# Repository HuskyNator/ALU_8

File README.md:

# ALU_8
_A tiny 8-bit ALU PCB project._

This project is limited to the use of very simple components, including the use of 7400 IC's with only rudementary behaviour. (This also excludes a clock, though I might add one in the future.)

Note this is a first-time learning project, both with respect to [KiCad](https://www.kicad.org/) and PCB design as a whole. Feel free to give tips or insights!

## Design
>_TODO_

---
### Issues
#### Input Switching:
In an attempt to emulate T-flip-flop-like switching behaviour on the input I've opted to use a leader-follower approach. This is quite bulky & resource intensive. Alternative solutions may include:
- Changing the fysical input mechanic; although I'm unaware of a suitable solution
- Adding a clock & using actual T-flip-flops
- Using an analogue solution; of which there seem multiple, though I'm unsure about the design intricacies involved (especially since this seems unorthodox & design-flaw-sensitive).

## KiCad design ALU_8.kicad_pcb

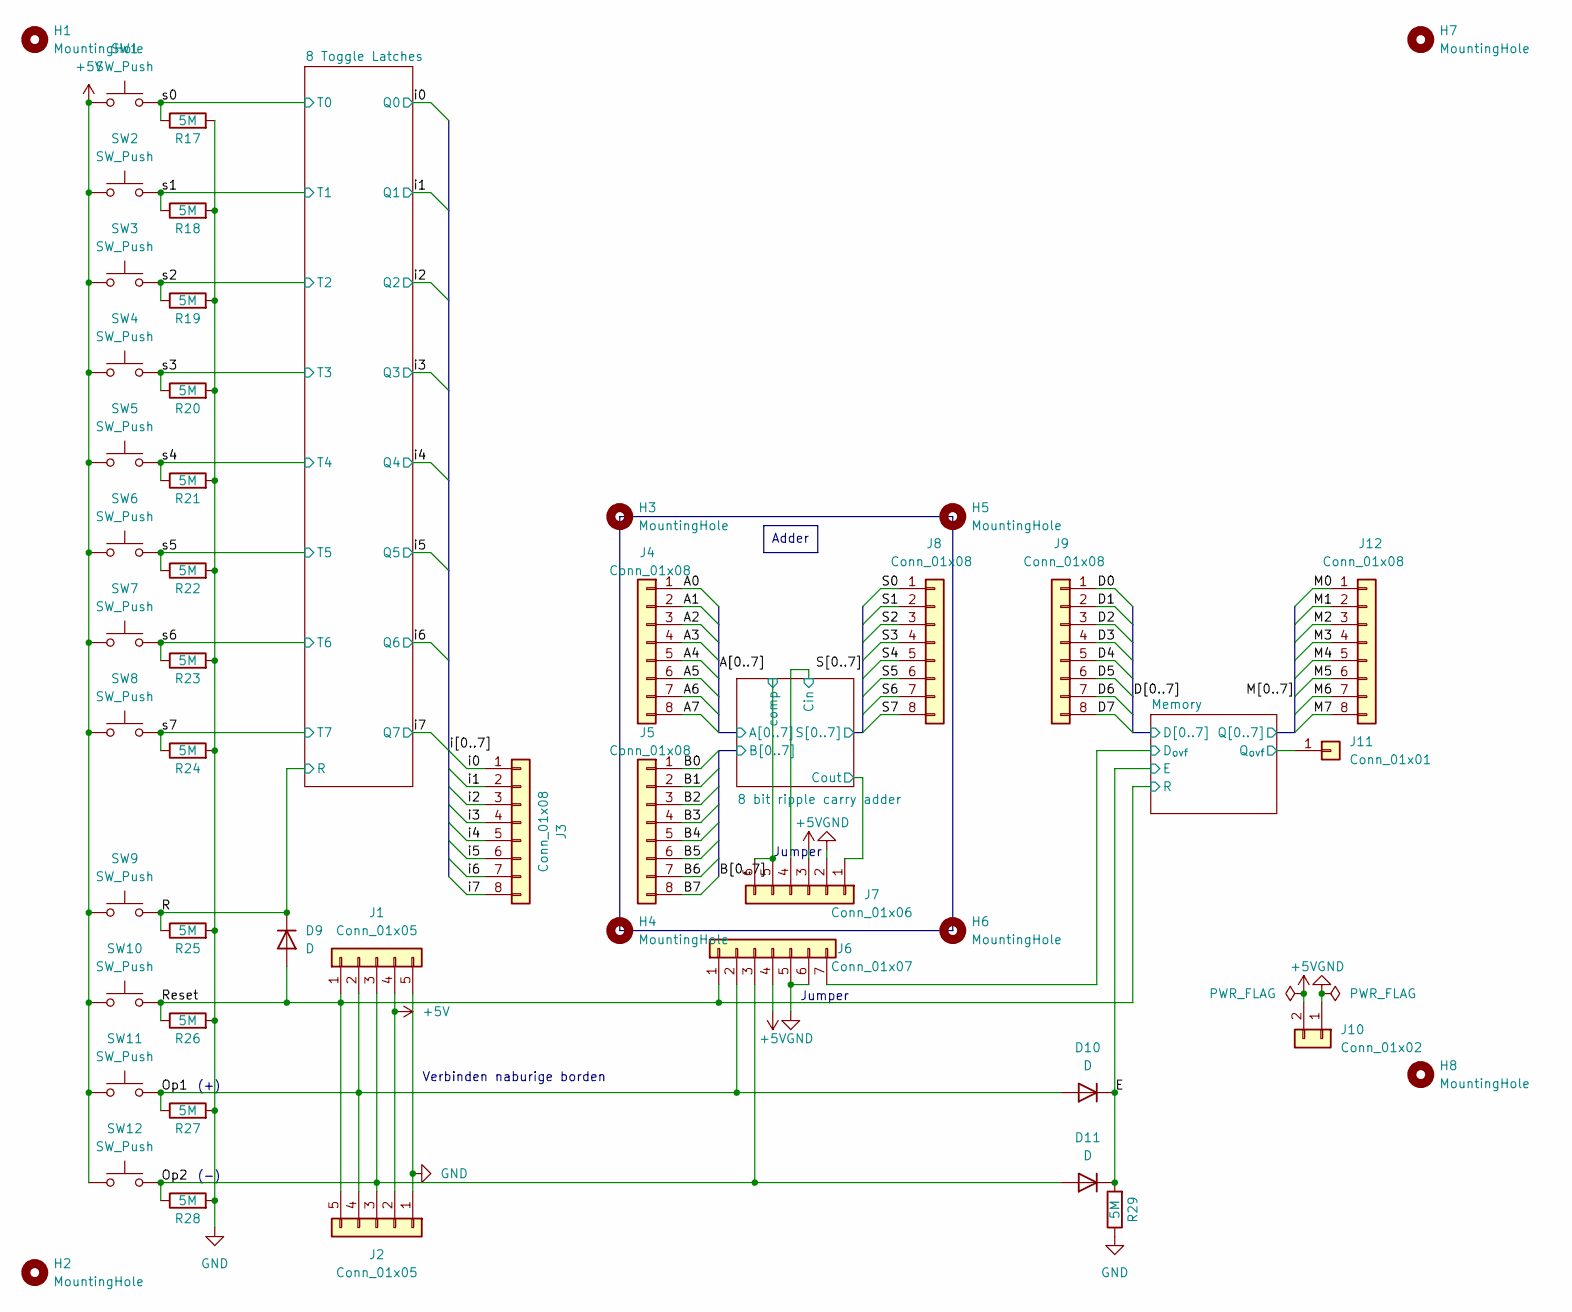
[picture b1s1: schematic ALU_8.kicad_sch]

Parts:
D9, D10, D11: D; D_DO-15_P15.24mm_Horizontal
H1, H2, H3, H4, H5, H6, H7, H8: MountingHole; MountingHole_5mm
J1, J2: Conn_01x05; PinHeader_1x05_P2.54mm_Horizontal
J3, J4, J5, J8, J9, J12: Conn_01x08; PinHeader_1x08_P2.54mm_Vertical
J6: Conn_01x07; PinHeader_1x07_P2.54mm_Vertical
J7: Conn_01x06; PinHeader_1x06_P2.54mm_Vertical
J10: Conn_01x02; PinHeader_1x02_P2.54mm_Vertical
J11: Conn_01x01; PinHeader_1x01_P2.54mm_Vertical
R17, R18, R19, R20, R21, R22, R23, R24, R25, R26, R27, R28, R29: 5M; R_Axial_DIN0207_L6.3mm_D2.5mm_P7.62mm_Horizontal
SW1, SW2, SW3, SW4, SW5, SW6, SW7, SW8, SW9, SW10, SW11, SW12: SW_Push; SW_PUSH_6mm_H13mm

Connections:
+5V: J1.4, J2.2, J6.4, J7.3, J10.2, SW1.1, SW2.1, SW3.1, SW4.1, SW5.1, SW6.1, SW7.1, SW8.1, SW9.1, SW10.1, SW11.1, SW12.1; also elsewhere on the board
/8 bit ripple carry adder/Cin: J7.4; also elsewhere on the board
/8 bit ripple carry adder/Cout: J7.1; also elsewhere on the board
/8 bit ripple carry adder/comp: J7.5, J7.6; also elsewhere on the board
/A0: J4.1; also elsewhere on the board
/A1: J4.2; also elsewhere on the board
/A2: J4.3; also elsewhere on the board
/A3: J4.4; also elsewhere on the board
/A4: J4.5; also elsewhere on the board
/A5: J4.6; also elsewhere on the board
/A6: J4.7; also elsewhere on the board
/A7: J4.8; also elsewhere on the board
/B0: J5.1; also elsewhere on the board
/B1: J5.2; also elsewhere on the board
/B2: J5.3; also elsewhere on the board
/B3: J5.4; also elsewhere on the board
/B4: J5.5; also elsewhere on the board
/B5: J5.6; also elsewhere on the board
/B6: J5.7; also elsewhere on the board
/B7: J5.8; also elsewhere on the board
/D0: J9.1; also elsewhere on the board
/D1: J9.2; also elsewhere on the board
/D2: J9.3; also elsewhere on the board
/D3: J9.4; also elsewhere on the board
/D4: J9.5; also elsewhere on the board
/D5: J9.6; also elsewhere on the board
/D6: J9.7; also elsewhere on the board
/D7: J9.8; also elsewhere on the board
/E: D10.1 (K), D11.1 (K), R29.2; also elsewhere on the board
/M0: J12.1; also elsewhere on the board
/M1: J12.2; also elsewhere on the board
/M2: J12.3; also elsewhere on the board
/M3: J12.4; also elsewhere on the board
/M4: J12.5; also elsewhere on the board
/M5: J12.6; also elsewhere on the board
/M6: J12.7; also elsewhere on the board
/M7: J12.8; also elsewhere on the board
/Memory/D_{ovf}: J6.7; also elsewhere on the board
/Memory/Q_{ovf}: J11.1; also elsewhere on the board
/Op1: D10.2 (A), J1.2, J2.4, J6.2, R27.1, SW11.2
/Op2: D11.2 (A), J1.3, J2.3, J6.3, R28.1, SW12.2
/R: D9.1 (K), R25.1, SW9.2; also elsewhere on the board
/Reset: D9.2 (A), J1.1, J2.5, J6.1, R26.1, SW10.2; also elsewhere on the board
/S0: J8.1; also elsewhere on the board
/S1: J8.2; also elsewhere on the board
/S2: J8.3; also elsewhere on the board
/S3: J8.4; also elsewhere on the board
/S4: J8.5; also elsewhere on the board
/S5: J8.6; also elsewhere on the board
/S6: J8.7; also elsewhere on the board
/S7: J8.8; also elsewhere on the board
/i0: J3.1; also elsewhere on the board
/i1: J3.2; also elsewhere on the board
/i2: J3.3; also elsewhere on the board
/i3: J3.4; also elsewhere on the board
/i4: J3.5; also elsewhere on the board
/i5: J3.6; also elsewhere on the board
/i6: J3.7; also elsewhere on the board
/i7: J3.8; also elsewhere on the board
/s0: R17.1, SW1.2; also elsewhere on the board
/s1: R18.1, SW2.2; also elsewhere on the board
/s2: R19.1, SW3.2; also elsewhere on the board
/s3: R20.1, SW4.2; also elsewhere on the board
/s4: R21.1, SW5.2; also elsewhere on the board
/s5: R22.1, SW6.2; also elsewhere on the board
/s6: R23.1, SW7.2; also elsewhere on the board
/s7: R24.1, SW8.2; also elsewhere on the board
GND: J1.5, J2.1, J6.5, J6.6, J7.2, J10.1, R17.2, R18.2, R19.2, R20.2, R21.2, R22.2, R23.2, R24.2, R25.2, R26.2, R27.2, R28.2, R29.1; also elsewhere on the board

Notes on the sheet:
Adder
(-)
Jumper
Verbinden naburige borden
(+)

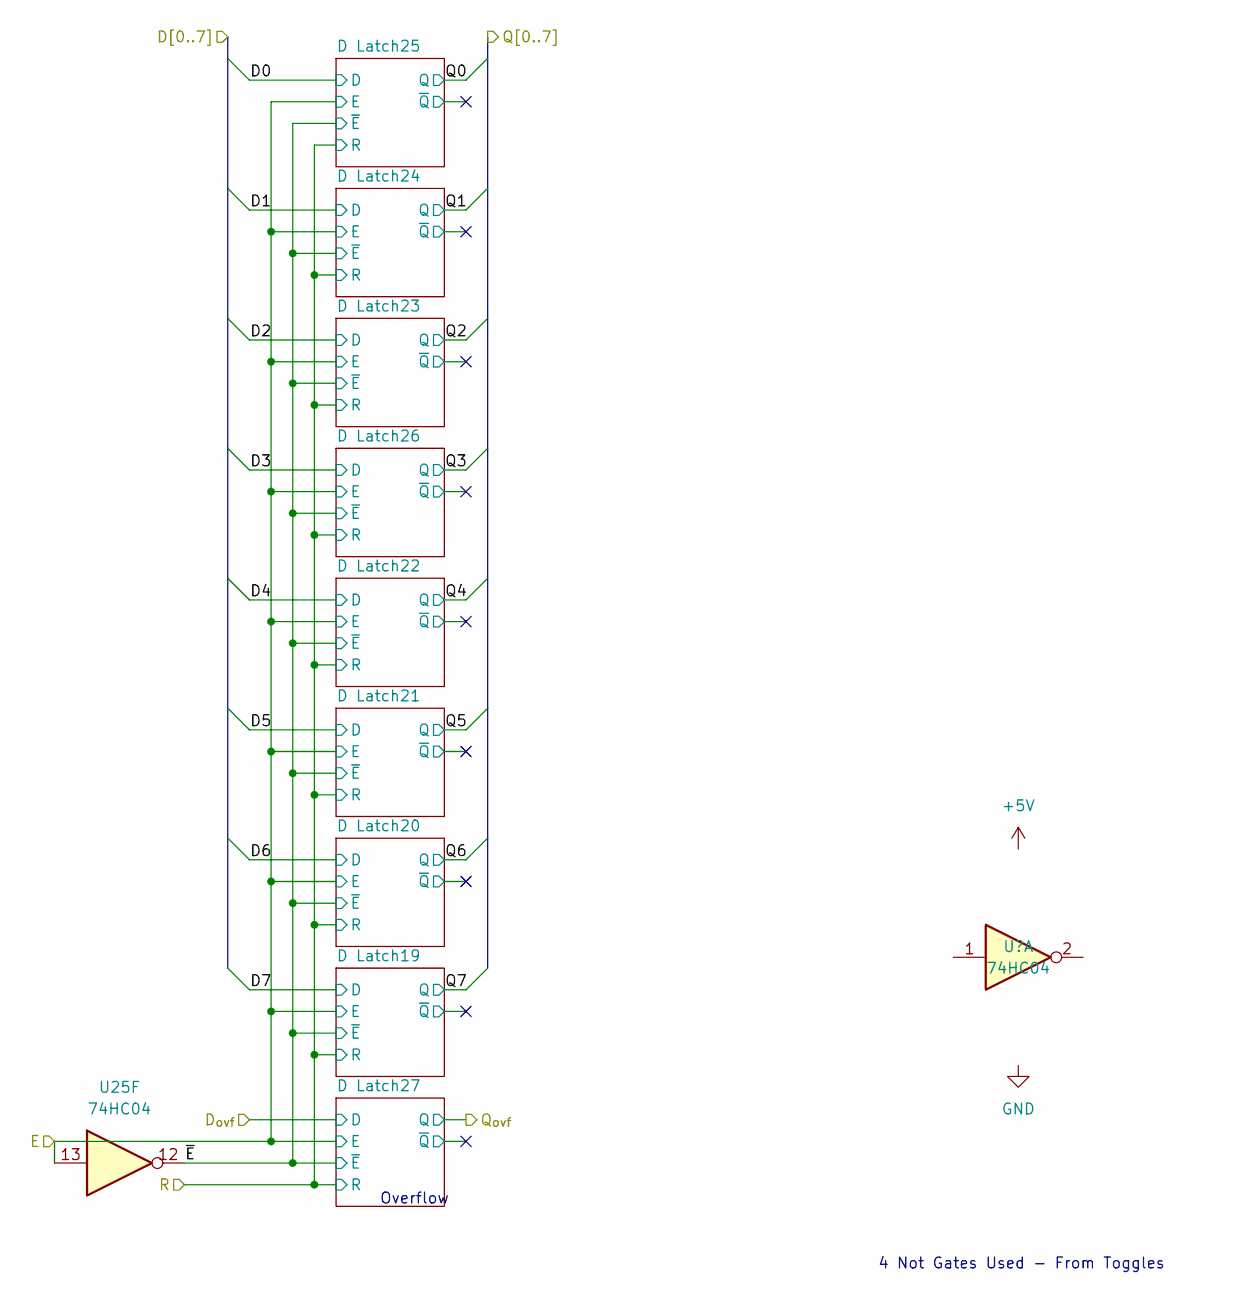
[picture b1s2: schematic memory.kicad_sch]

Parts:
U25: 74HC04; DIP-14_W7.62mm_Socket

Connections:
+5V: U25.14 (VCC); also elsewhere on the board
/D0: U25.1; also elsewhere on the board
/D1: U25.3; also elsewhere on the board
/D2: U25.5; also elsewhere on the board
/D7: U25.9; also elsewhere on the board
/E: U25.13; also elsewhere on the board
/Memory/D_{ovf}: U25.11; also elsewhere on the board
/Memory/~E: U25.12; also elsewhere on the board
GND: U25.7 (GND); also elsewhere on the board
unnamed 248: U25.2; also elsewhere on the board
unnamed 249: U25.4; also elsewhere on the board
unnamed 250: U25.6; also elsewhere on the board
unnamed 251: U25.8; also elsewhere on the board
unnamed 252: U25.10; also elsewhere on the board

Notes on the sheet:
4 Not Gates Used - From Toggles
Overflow

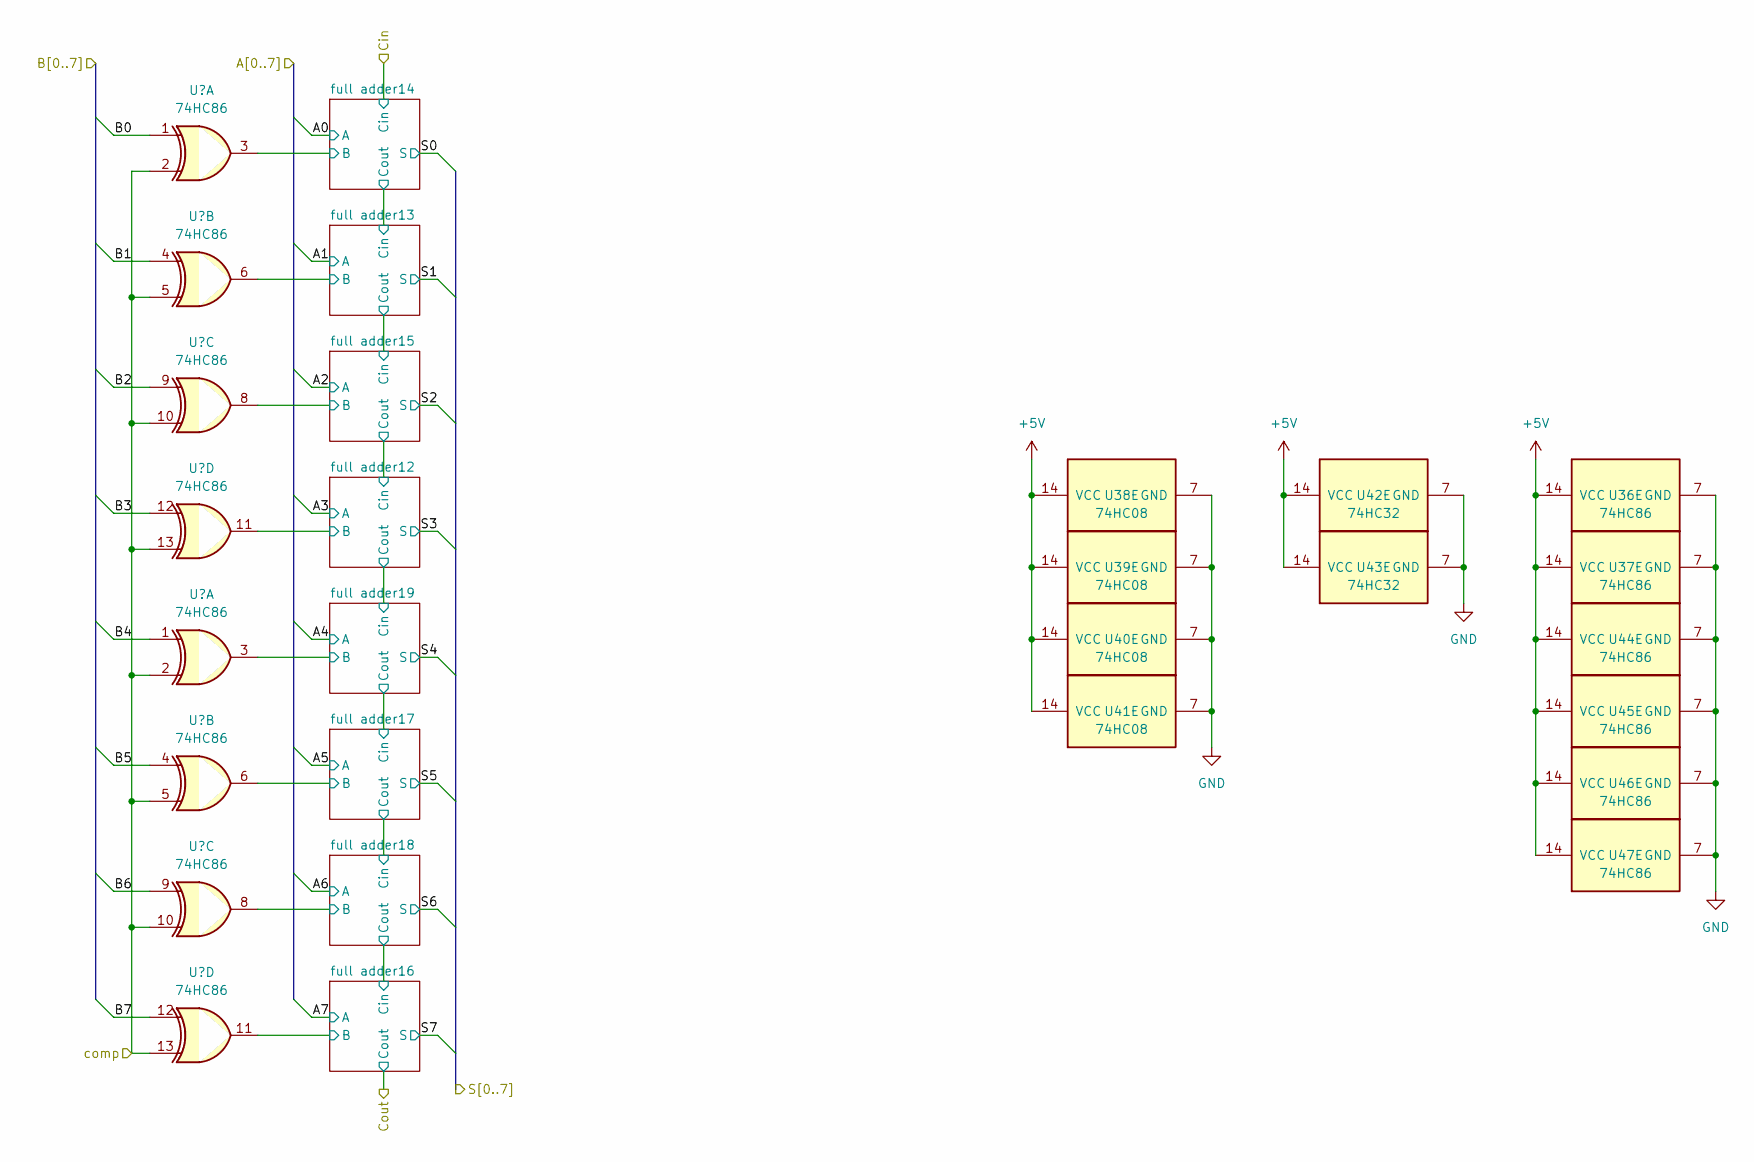
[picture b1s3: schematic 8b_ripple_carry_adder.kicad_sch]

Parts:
U36, U37, U44, U45, U46, U47: 74HC86; DIP-14_W7.62mm_Socket
U38, U39, U40, U41: 74HC08; DIP-14_W7.62mm_Socket
U42, U43: 74HC32; DIP-14_W7.62mm_Socket

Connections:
+5V: U36.14 (VCC), U37.14 (VCC), U38.14 (VCC), U39.14 (VCC), U40.14 (VCC), U41.14 (VCC), U42.14 (VCC), U43.14 (VCC), U44.14 (VCC), U45.14 (VCC), U46.14 (VCC), U47.14 (VCC); also elsewhere on the board
/8 bit ripple carry adder/Cout: U43.11; also elsewhere on the board
/8 bit ripple carry adder/comp: U36.2, U36.5, U36.10, U36.13, U37.2, U37.5, U37.10, U37.13; also elsewhere on the board
/8 bit ripple carry adder/full adder12/B: U36.11, U38.10, U44.12
/8 bit ripple carry adder/full adder12/Cin: U39.10, U42.8, U45.12
/8 bit ripple carry adder/full adder12/Cout: U42.11; also elsewhere on the board
/8 bit ripple carry adder/full adder12/g: U38.8, U42.12
/8 bit ripple carry adder/full adder12/p: U39.9, U44.11, U45.13
/8 bit ripple carry adder/full adder13/B: U36.6, U38.5, U44.4
/8 bit ripple carry adder/full adder13/Cin: U39.5, U45.4; also elsewhere on the board
/8 bit ripple carry adder/full adder13/Cout: U39.13, U42.6, U45.9
/8 bit ripple carry adder/full adder13/g: U38.6, U42.4
/8 bit ripple carry adder/full adder13/p: U39.4, U44.6, U45.5
/8 bit ripple carry adder/full adder14/B: U36.3; also elsewhere on the board
/8 bit ripple carry adder/full adder15/B: U36.8, U38.13, U44.9
/8 bit ripple carry adder/full adder15/g: U38.11, U42.9
/8 bit ripple carry adder/full adder15/p: U39.12, U44.8, U45.10
/8 bit ripple carry adder/full adder16/B: U37.11, U41.10, U46.12
/8 bit ripple carry adder/full adder16/Cin: U43.8, U47.12; also elsewhere on the board
/8 bit ripple carry adder/full adder16/g: U41.8, U43.12
/8 bit ripple carry adder/full adder16/p: U46.11, U47.13; also elsewhere on the board
/8 bit ripple carry adder/full adder17/B: U37.6, U41.5, U46.4
/8 bit ripple carry adder/full adder17/Cin: U47.4; also elsewhere on the board
/8 bit ripple carry adder/full adder17/Cout: U43.6, U47.9; also elsewhere on the board
/8 bit ripple carry adder/full adder17/g: U41.6, U43.4
/8 bit ripple carry adder/full adder17/p: U46.6, U47.5; also elsewhere on the board
/8 bit ripple carry adder/full adder18/B: U37.8, U41.13, U46.9
/8 bit ripple carry adder/full adder18/g: U41.11, U43.9
/8 bit ripple carry adder/full adder18/p: U46.8, U47.10; also elsewhere on the board
/8 bit ripple carry adder/full adder19/B: U37.3; also elsewhere on the board
/A1: U38.4, U44.5; also elsewhere on the board
/A2: U38.12, U44.10; also elsewhere on the board
/A3: U38.9, U44.13; also elsewhere on the board
/A5: U41.4, U46.5; also elsewhere on the board
/A6: U41.12, U46.10; also elsewhere on the board
/A7: U41.9, U46.13; also elsewhere on the board
/B0: U36.1; also elsewhere on the board
/B1: U36.4; also elsewhere on the board
/B2: U36.9; also elsewhere on the board
/B3: U36.12; also elsewhere on the board
/B4: U37.1; also elsewhere on the board
/B5: U37.4; also elsewhere on the board
/B6: U37.9; also elsewhere on the board
/B7: U37.12; also elsewhere on the board
/S1: U45.6; also elsewhere on the board
/S2: U45.8; also elsewhere on the board
/S3: U45.11; also elsewhere on the board
/S5: U47.6; also elsewhere on the board
/S6: U47.8; also elsewhere on the board
/S7: U47.11; also elsewhere on the board
GND: U36.7 (GND), U37.7 (GND), U38.7 (GND), U39.7 (GND), U40.7 (GND), U41.7 (GND), U42.7 (GND), U43.7 (GND), U44.7 (GND), U45.7 (GND), U46.7 (GND), U47.7 (GND); also elsewhere on the board
unnamed: U39.6, U42.5
unnamed: U39.8, U42.13
unnamed: U39.11, U42.10
unnamed 288: U43.5; also elsewhere on the board
unnamed 289: U43.10; also elsewhere on the board
unnamed 290: U43.13; also elsewhere on the board

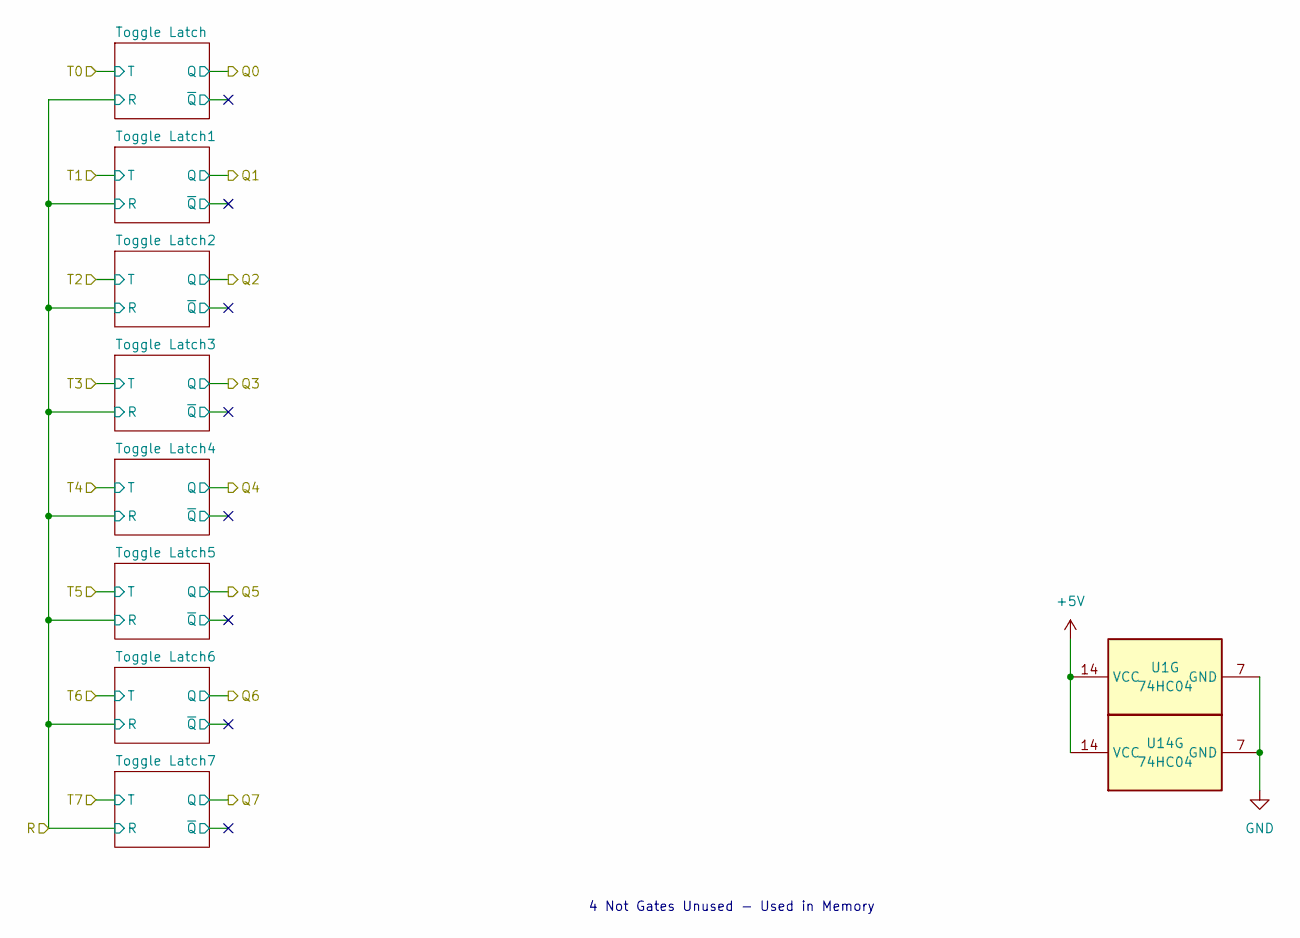
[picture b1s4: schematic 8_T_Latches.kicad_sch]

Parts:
U1, U14: 74HC04; DIP-14_W7.62mm_Socket

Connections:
+5V: U1.14 (VCC), U14.14 (VCC); also elsewhere on the board
/D3: U14.9; also elsewhere on the board
/D4: U14.11; also elsewhere on the board
/D5: U14.13; also elsewhere on the board
/D6: U14.5; also elsewhere on the board
/s1: U1.3; also elsewhere on the board
/s2: U1.5; also elsewhere on the board
/s3: U1.9; also elsewhere on the board
/s4: U1.11; also elsewhere on the board
/s5: U1.13; also elsewhere on the board
/s7: U14.3; also elsewhere on the board
GND: U1.7 (GND), U14.7 (GND); also elsewhere on the board
unnamed 174: U1.4; also elsewhere on the board
unnamed 175: U1.6; also elsewhere on the board
unnamed 176: U1.8; also elsewhere on the board
unnamed 177: U1.10; also elsewhere on the board
unnamed 178: U1.12; also elsewhere on the board
unnamed 216: U14.4; also elsewhere on the board
unnamed 217: U14.6; also elsewhere on the board
unnamed 218: U14.8; also elsewhere on the board
unnamed 219: U14.10; also elsewhere on the board
unnamed 220: U14.12; also elsewhere on the board

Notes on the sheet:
4 Not Gates Unused - Used in Memory

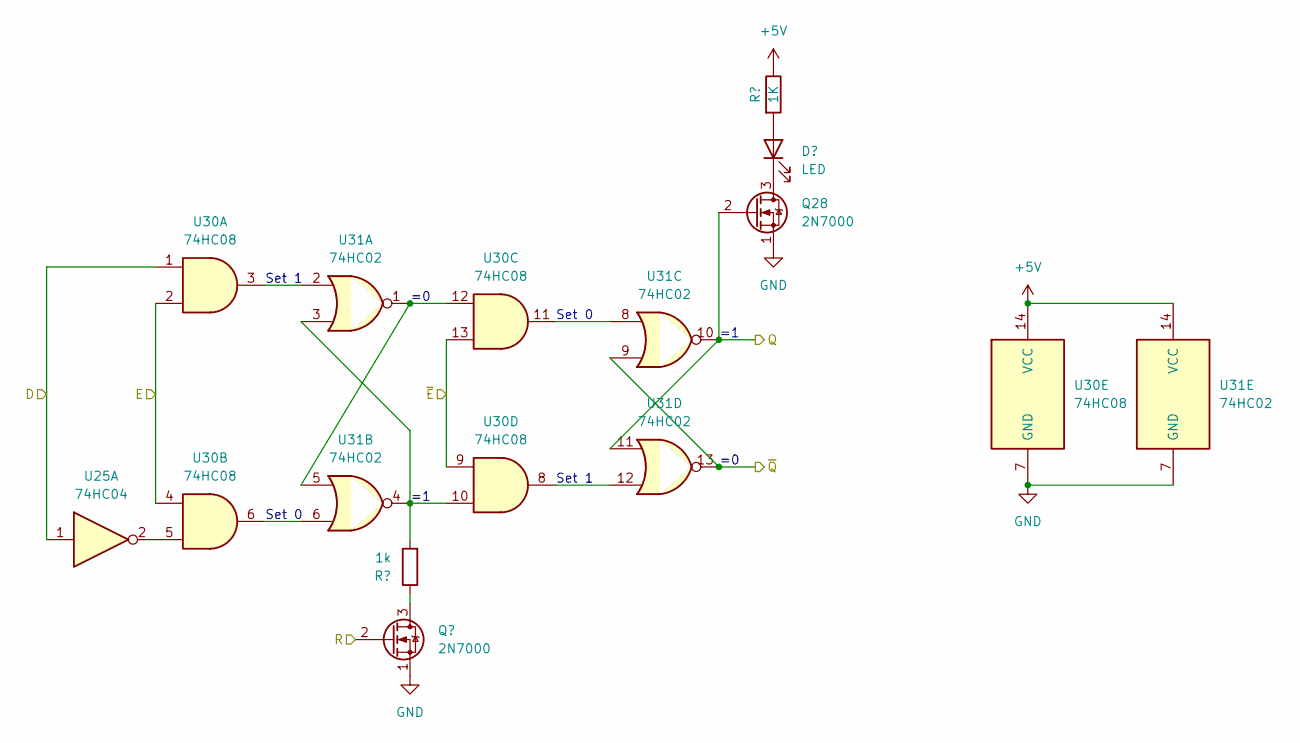
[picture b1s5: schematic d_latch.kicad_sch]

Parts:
D12: LED; D_DO-34_SOD68_P2.54mm_Vertical_KathodeUp
Q17, Q28: 2N7000; TO-92_Inline
R30: 1k; R_Axial_DIN0207_L6.3mm_D2.5mm_P7.62mm_Horizontal
R31: 1K; R_Axial_DIN0207_L6.3mm_D2.5mm_P7.62mm_Horizontal
U25: 74HC04; DIP-14_W7.62mm_Socket
U30: 74HC08; DIP-14_W7.62mm_Socket
U31: 74HC02; DIP-14_W7.62mm_Socket

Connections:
+5V: R31.1, U25.14 (VCC), U30.14 (VCC), U31.14 (VCC); also elsewhere on the board
/D0: U25.1, U30.1; also elsewhere on the board
/D1: U25.3; also elsewhere on the board
/D2: U25.5; also elsewhere on the board
/D7: U25.9; also elsewhere on the board
/E: U30.2, U30.4; also elsewhere on the board
/M0: Q28.2 (G), U31.10, U31.11; also elsewhere on the board
/Memory/D Latch25/~Q: U31.9, U31.13
/Memory/D_{ovf}: U25.11; also elsewhere on the board
/Memory/~E: U30.9, U30.13; also elsewhere on the board
/Reset: Q17.2 (G); also elsewhere on the board
GND: Q17.1 (S), Q28.1 (S), U25.7 (GND), U30.7 (GND), U31.7 (GND); also elsewhere on the board
unnamed: D12.2 (A), R31.2
unnamed: Q17.3 (D), R30.1
unnamed: U25.2, U30.5
unnamed 249: U25.4; also elsewhere on the board
unnamed 250: U25.6; also elsewhere on the board
unnamed 251: U25.8; also elsewhere on the board
unnamed 252: U25.10; also elsewhere on the board
unnamed: U30.3, U31.2
unnamed: U30.6, U31.6
unnamed: U30.8, U31.12
unnamed: U30.11, U31.8
unnamed: U30.12, U31.1, U31.5

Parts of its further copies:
D13, D14, D15, D16, D17, D18, D19, D20: LED; D_DO-34_SOD68_P2.54mm_Vertical_KathodeUp
Q18, Q19, Q20, Q21, Q22, Q23, Q24, Q25, Q26, Q27, Q29, Q30, Q31, Q32, Q33, Q34: 2N7000; TO-92_Inline
R32, R34, R36, R38, R40, R42, R44, R46: 1k; R_Axial_DIN0207_L6.3mm_D2.5mm_P7.62mm_Horizontal
R33, R35, R37, R39, R41, R43, R45, R47: 1K; R_Axial_DIN0207_L6.3mm_D2.5mm_P7.62mm_Horizontal
U19, U21, U23, U26, U28, U32, U34, U49: 74HC08; DIP-14_W7.62mm_Socket
U20, U22, U24, U27, U29, U33, U35, U48: 74HC02; DIP-14_W7.62mm_Socket

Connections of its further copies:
+5V: R33.1, R35.1, R37.1, R39.1, R41.1, R43.1, R45.1, R47.1, U19.14 (VCC), U20.14 (VCC), U21.14 (VCC), U22.14 (VCC), U23.14 (VCC), U24.14 (VCC), U26.14 (VCC), U27.14 (VCC), U28.14 (VCC), U29.14 (VCC), U32.14 (VCC), U33.14 (VCC), U34.14 (VCC), U35.14 (VCC), U48.14 (VCC), U49.14 (VCC); also elsewhere on the board
/8 bit ripple carry adder/full adder12/Cout: U49.2; also elsewhere on the board
/8 bit ripple carry adder/full adder16/Cin: U49.10; also elsewhere on the board
/8 bit ripple carry adder/full adder16/p: U49.9; also elsewhere on the board
/8 bit ripple carry adder/full adder17/Cin: U49.5; also elsewhere on the board
/8 bit ripple carry adder/full adder17/Cout: U49.13; also elsewhere on the board
/8 bit ripple carry adder/full adder17/p: U49.4; also elsewhere on the board
/8 bit ripple carry adder/full adder18/p: U49.12; also elsewhere on the board
/8 bit ripple carry adder/full adder19/p: U49.1; also elsewhere on the board
/D1: U28.1; also elsewhere on the board
/D2: U26.1; also elsewhere on the board
/D3: U32.1; also elsewhere on the board
/D4: U23.1; also elsewhere on the board
/D5: U21.1; also elsewhere on the board
/D6: U19.1; also elsewhere on the board
/E: U19.2, U19.4, U21.2, U21.4, U23.2, U23.4, U26.2, U26.4, U28.2, U28.4, U32.2, U32.4, U34.2, U34.4; also elsewhere on the board
/M1: Q26.2 (G), U29.10, U29.11; also elsewhere on the board
/M2: Q24.2 (G), U27.10, U27.11; also elsewhere on the board
/M3: Q30.2 (G), U33.10, U33.11; also elsewhere on the board
/M4: Q22.2 (G), U24.10, U24.11; also elsewhere on the board
/M5: Q20.2 (G), U22.10, U22.11; also elsewhere on the board
/M6: Q18.2 (G), U20.10, U20.11; also elsewhere on the board
/M7: Q34.2 (G), U48.10, U48.11; also elsewhere on the board
/Memory/D Latch19/~Q: U48.9, U48.13
/Memory/D Latch20/~Q: U20.9, U20.13
/Memory/D Latch21/~Q: U22.9, U22.13
/Memory/D Latch22/~Q: U24.9, U24.13
/Memory/D Latch23/~Q: U27.9, U27.13
/Memory/D Latch24/~Q: U29.9, U29.13
/Memory/D Latch26/~Q: U33.9, U33.13
/Memory/D Latch27/~Q: U35.9, U35.13
/Memory/D_{ovf}: U34.1; also elsewhere on the board
/Memory/Q_{ovf}: Q32.2 (G), U35.10, U35.11; also elsewhere on the board
/Memory/~E: U19.9, U19.13, U21.9, U21.13, U23.9, U23.13, U26.9, U26.13, U28.9, U28.13, U32.9, U32.13, U34.9, U34.13; also elsewhere on the board
/Reset: Q19.2 (G), Q21.2 (G), Q23.2 (G), Q25.2 (G), Q27.2 (G), Q29.2 (G), Q31.2 (G), Q33.2 (G); also elsewhere on the board
GND: Q18.1 (S), Q19.1 (S), Q20.1 (S), Q21.1 (S), Q22.1 (S), Q23.1 (S), Q24.1 (S), Q25.1 (S), Q26.1 (S), Q27.1 (S), Q29.1 (S), Q30.1 (S), Q31.1 (S), Q32.1 (S), Q33.1 (S), Q34.1 (S), U19.7 (GND), U20.7 (GND), U21.7 (GND), U22.7 (GND), U23.7 (GND), U24.7 (GND), U26.7 (GND), U27.7 (GND), U28.7 (GND), U29.7 (GND), U32.7 (GND), U33.7 (GND), U34.7 (GND), U35.7 (GND), U48.7 (GND), U49.7 (GND); also elsewhere on the board
unnamed: D13.2 (A), R33.2
unnamed: D13.1 (K), Q20.3 (D)
unnamed: D14.2 (A), R35.2
unnamed: D14.1 (K), Q22.3 (D)
unnamed: D15.2 (A), R37.2
unnamed: D15.1 (K), Q24.3 (D)
unnamed: D16.2 (A), R39.2
unnamed: D16.1 (K), Q26.3 (D)
unnamed: D17.2 (A), R41.2
unnamed: D18.2 (A), R43.2
unnamed: D18.1 (K), Q30.3 (D)
unnamed: D19.2 (A), R45.2
unnamed: D19.1 (K), Q32.3 (D)
unnamed: D20.2 (A), R47.2
unnamed: D20.1 (K), Q34.3 (D)
unnamed: Q19.3 (D), R32.1
unnamed: Q21.3 (D), R34.1
unnamed: Q23.3 (D), R36.1
unnamed: Q25.3 (D), R38.1
unnamed: Q27.3 (D), R40.1
unnamed: Q29.3 (D), R42.1
unnamed: Q31.3 (D), R44.1
unnamed: Q33.3 (D), R46.1
unnamed: R32.2, U21.10, U22.3, U22.4
unnamed 167: R34.2, U23.10, U24.3, U24.4; also elsewhere on the board
unnamed: R36.2, U26.10, U27.3, U27.4
unnamed: R38.2, U28.10, U29.3, U29.4
unnamed: R42.2, U32.10, U33.3, U33.4
unnamed: R44.2, U34.10, U35.3, U35.4
unnamed 172: R46.2, U48.3, U48.4; also elsewhere on the board
unnamed 217: U19.5; also elsewhere on the board
unnamed 218: U32.5; also elsewhere on the board
unnamed 219: U23.5; also elsewhere on the board
unnamed 220: U21.5; also elsewhere on the board
unnamed: U19.3, U20.2
unnamed: U19.6, U20.6
unnamed: U19.8, U20.12
unnamed: U19.11, U20.8
unnamed: U19.12, U20.1, U20.5
unnamed: U21.3, U22.2
unnamed: U21.6, U22.6
unnamed: U21.8, U22.12
unnamed: U21.11, U22.8
unnamed: U21.12, U22.1, U22.5
unnamed 243: U23.3, U24.2; also elsewhere on the board
unnamed 244: U23.6, U24.6; also elsewhere on the board
unnamed 245: U23.8, U24.12; also elsewhere on the board
unnamed 246: U23.11, U24.8; also elsewhere on the board
unnamed 247: U23.12, U24.1, U24.5; also elsewhere on the board
unnamed 249: U28.5; also elsewhere on the board
unnamed 250: U26.5; also elsewhere on the board
unnamed 252: U34.5; also elsewhere on the board
unnamed: U26.3, U27.2
unnamed: U26.6, U27.6
unnamed: U26.8, U27.12
unnamed: U26.11, U27.8
unnamed: U26.12, U27.1, U27.5
unnamed: U28.3, U29.2
unnamed: U28.6, U29.6
unnamed: U28.8, U29.12
unnamed: U28.11, U29.8
unnamed: U28.12, U29.1, U29.5
unnamed: U32.3, U33.2
unnamed: U32.6, U33.6
unnamed: U32.8, U33.12
unnamed: U32.11, U33.8
unnamed: U32.12, U33.1, U33.5
unnamed: U34.3, U35.2
unnamed: U34.6, U35.6
unnamed: U34.8, U35.12
unnamed: U34.11, U35.8
unnamed: U34.12, U35.1, U35.5
unnamed 282: U48.2; also elsewhere on the board
unnamed 283: U48.6; also elsewhere on the board
unnamed 284: U48.12; also elsewhere on the board
unnamed 285: U48.8; also elsewhere on the board
unnamed 286: U48.1, U48.5; also elsewhere on the board
unnamed 287: U49.3; also elsewhere on the board
unnamed 288: U49.6; also elsewhere on the board
unnamed 289: U49.11; also elsewhere on the board
unnamed 290: U49.8; also elsewhere on the board

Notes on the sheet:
Set 0
Set 1

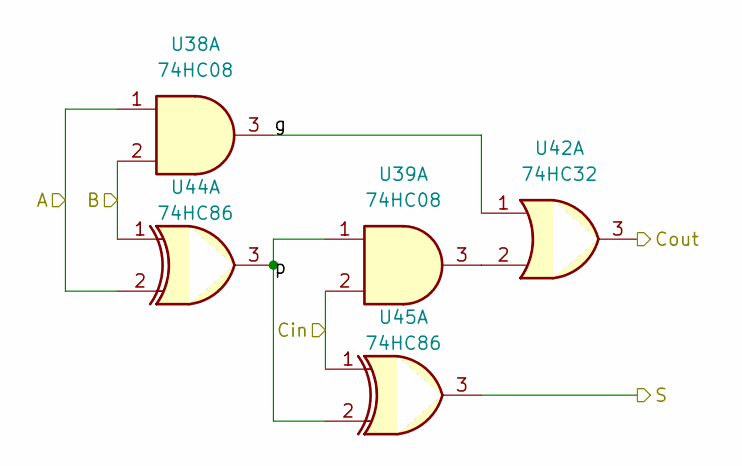
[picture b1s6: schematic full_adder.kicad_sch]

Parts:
U38, U39: 74HC08; DIP-14_W7.62mm_Socket
U42: 74HC32; DIP-14_W7.62mm_Socket
U44, U45: 74HC86; DIP-14_W7.62mm_Socket

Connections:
/8 bit ripple carry adder/Cin: U39.2, U45.1; also elsewhere on the board
/8 bit ripple carry adder/full adder12/B: U38.10, U44.12; also elsewhere on the board
/8 bit ripple carry adder/full adder12/Cin: U39.10, U42.8, U45.12
/8 bit ripple carry adder/full adder12/Cout: U42.11; also elsewhere on the board
/8 bit ripple carry adder/full adder12/g: U38.8, U42.12
/8 bit ripple carry adder/full adder12/p: U39.9, U44.11, U45.13
/8 bit ripple carry adder/full adder13/B: U38.5, U44.4; also elsewhere on the board
/8 bit ripple carry adder/full adder13/Cin: U39.5, U42.3, U45.4
/8 bit ripple carry adder/full adder13/Cout: U39.13, U42.6, U45.9
/8 bit ripple carry adder/full adder13/g: U38.6, U42.4
/8 bit ripple carry adder/full adder13/p: U39.4, U44.6, U45.5
/8 bit ripple carry adder/full adder14/B: U38.2, U44.1; also elsewhere on the board
/8 bit ripple carry adder/full adder14/g: U38.3, U42.1
/8 bit ripple carry adder/full adder14/p: U39.1, U44.3, U45.2
/8 bit ripple carry adder/full adder15/B: U38.13, U44.9; also elsewhere on the board
/8 bit ripple carry adder/full adder15/g: U38.11, U42.9
/8 bit ripple carry adder/full adder15/p: U39.12, U44.8, U45.10
/A0: U38.1, U44.2; also elsewhere on the board
/A1: U38.4, U44.5; also elsewhere on the board
/A2: U38.12, U44.10; also elsewhere on the board
/A3: U38.9, U44.13; also elsewhere on the board
/S0: U45.3; also elsewhere on the board
/S1: U45.6; also elsewhere on the board
/S2: U45.8; also elsewhere on the board
/S3: U45.11; also elsewhere on the board
unnamed: U39.3, U42.2
unnamed: U39.6, U42.5
unnamed: U39.8, U42.13
unnamed: U39.11, U42.10

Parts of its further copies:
U49: 74HC08; DIP-14_W7.62mm_Socket

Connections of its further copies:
+5V: U49.14 (VCC); also elsewhere on the board
/8 bit ripple carry adder/full adder12/Cout: U49.2; also elsewhere on the board
/8 bit ripple carry adder/full adder16/Cin: U49.10; also elsewhere on the board
/8 bit ripple carry adder/full adder16/p: U49.9; also elsewhere on the board
/8 bit ripple carry adder/full adder17/Cin: U49.5; also elsewhere on the board
/8 bit ripple carry adder/full adder17/Cout: U49.13; also elsewhere on the board
/8 bit ripple carry adder/full adder17/p: U49.4; also elsewhere on the board
/8 bit ripple carry adder/full adder18/p: U49.12; also elsewhere on the board
/8 bit ripple carry adder/full adder19/p: U49.1; also elsewhere on the board
GND: U49.7 (GND); also elsewhere on the board
unnamed 287: U49.3; also elsewhere on the board
unnamed 288: U49.6; also elsewhere on the board
unnamed 289: U49.11; also elsewhere on the board
unnamed 290: U49.8; also elsewhere on the board
